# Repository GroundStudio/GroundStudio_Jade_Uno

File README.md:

GroundStudio Jade Uno
====================================

Get it from [ardushop.ro](https://ardushop.ro/ro/home/1728-placa-de-dezvoltare-jade-uno.html)

Explore all the GroundStudio products at [GroundStudio.ro](https://groundstudio.ro/)

Description
-------------------
ATMEGA328P based development board, 32kBytes of In-System Self-Programmable Flash program memory,  1kBytes EEPROM, 2kBytes Internal SRAM, 6 PWM Channels, 20 Digital Pins including 4 channel 10 bit ADC Pins and HT42B534-2 for USB comunication.

Contents
-------------------

* [/Documentation](https://github.com/GroundStudio/GroundStudio_Jade_Uno/tree/main/Documentation) -- Pinout.
* [/Hardware](https://github.com/GroundStudio/GroundStudio_Jade_Uno/tree/main/Hardware) -- Schematics, layout.

Versions
-------------------
*(Not all tags shown)*

* [REV0.2]

License
-------------------

This is released under the [Attribution-ShareAlike 4.0 International (CC BY-SA 4.0)](https://creativecommons.org/licenses/by-sa/4.0/) license. 

Please consider contributing back to help the open-source hardware community continue to thrive and grow!

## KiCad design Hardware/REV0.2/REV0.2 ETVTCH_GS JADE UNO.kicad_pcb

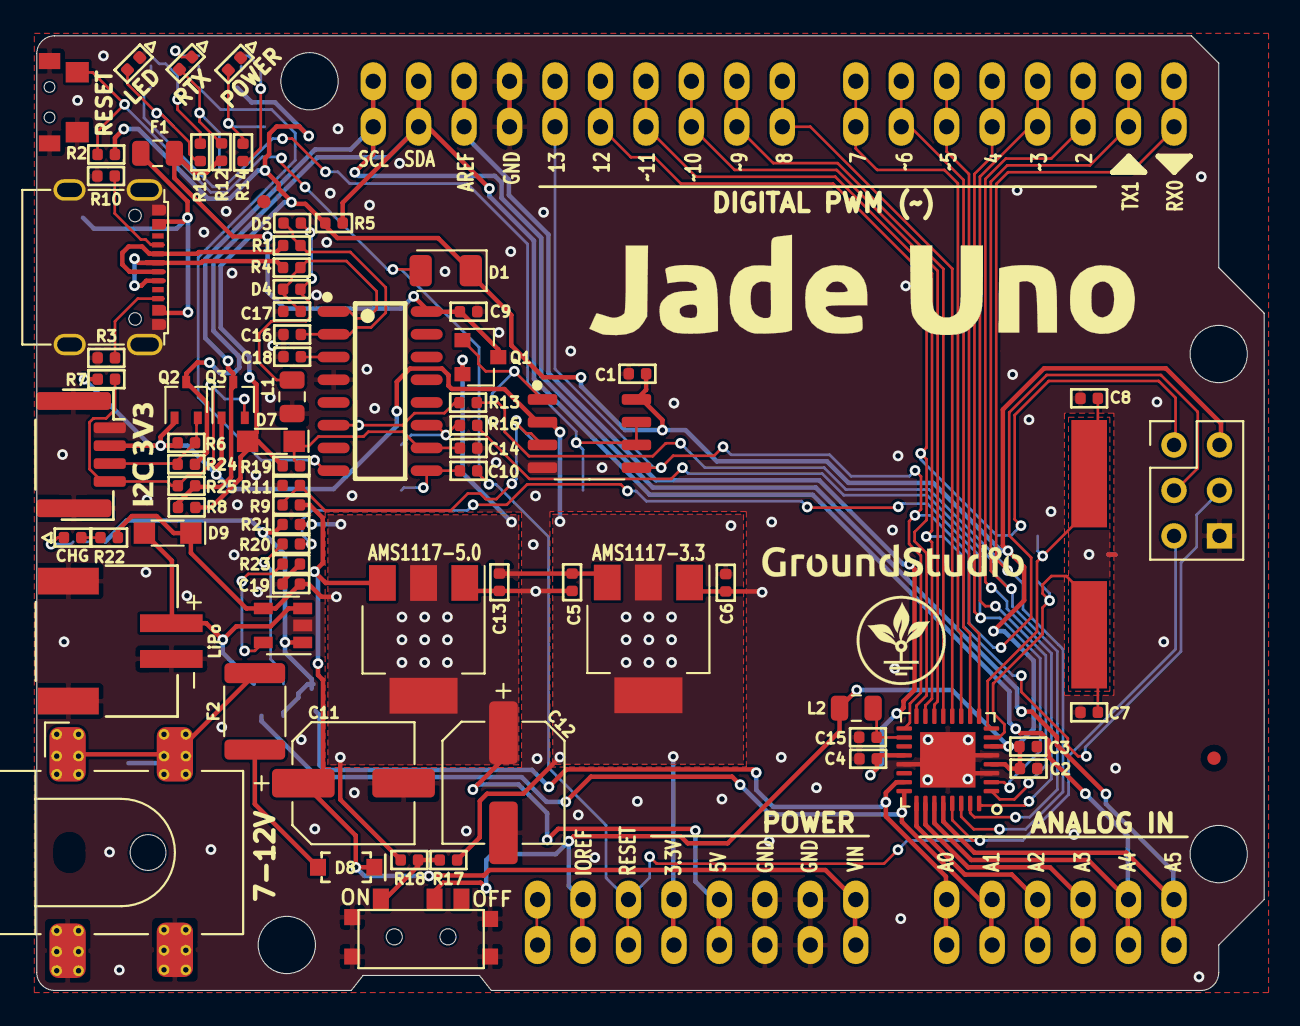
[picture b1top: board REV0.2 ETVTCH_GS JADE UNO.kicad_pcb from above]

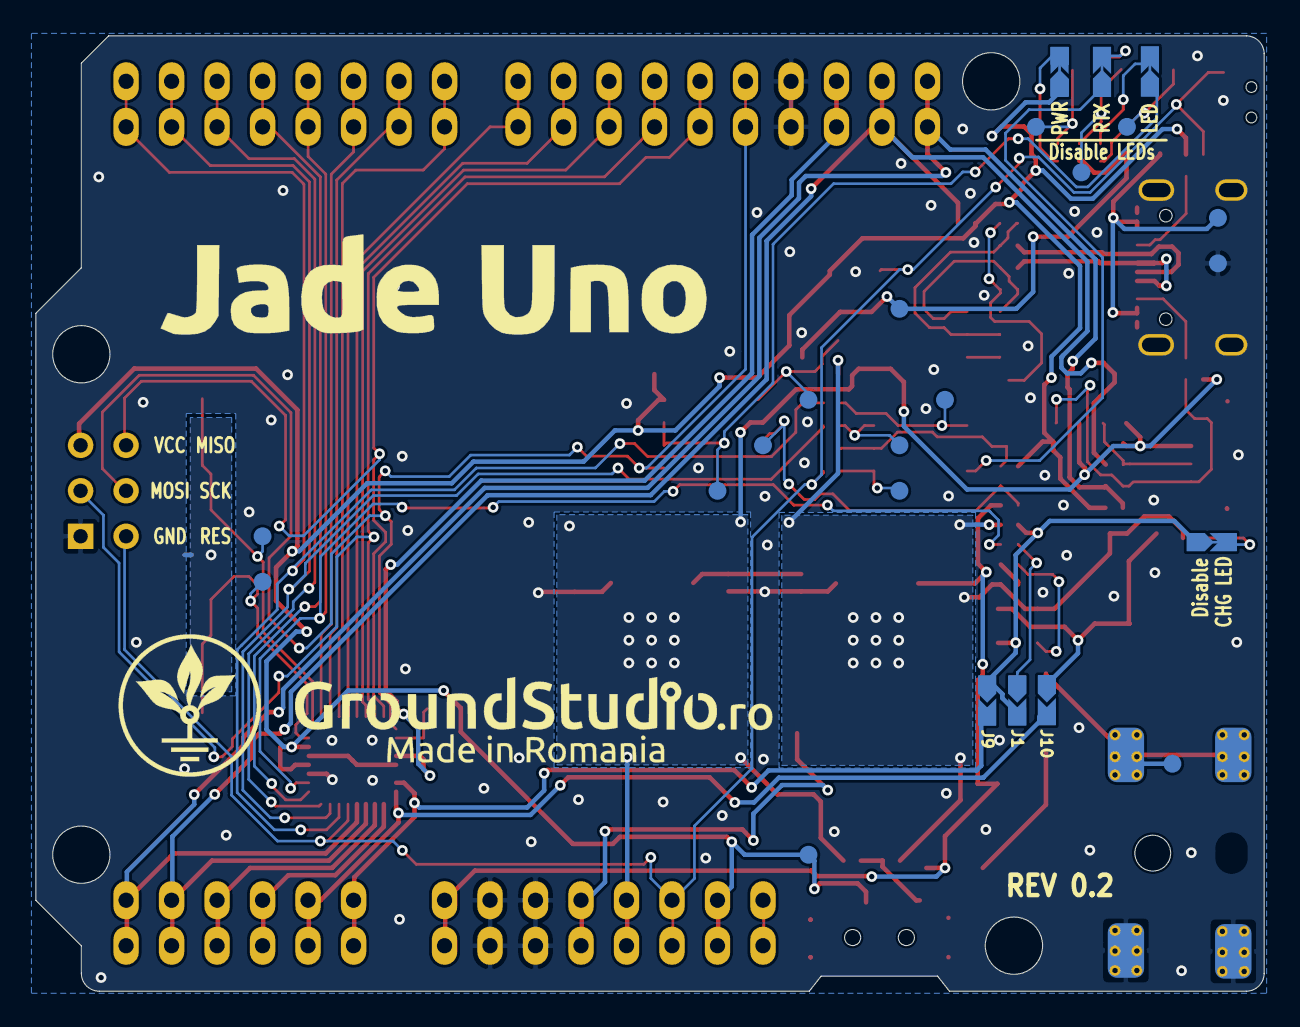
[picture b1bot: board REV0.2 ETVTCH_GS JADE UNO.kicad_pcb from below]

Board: 2 copper layers, 68.6 x 53.3 mm, 108 parts (11 on the bottom side), 66 nets.

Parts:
C1, C2, C3, C4, C9, C10, C13, C14, C15: C_0402_100nF_16V; C_0402
C5, C6: C_0402_10uF_10V; C_0402
C7, C8: C_0402_22pF_50V; C_0402
C11, C12: CP_Elec_6.3x5.4_47uF_25V; CP_Elec_6.3x5.4
C16, C17: C_0402_47pF_50V; C_0402
C18, C19: C_0402_1uF_10V; C_0402
D1: D_1206_CD1206-S01575; D_1206
D2, D6, D10: LED_0402_GREEN; LED_0402
D3: LED_0402_RED; LED_0402
D4, D5: R_0402_PS0402V014AT; R_0402
D7, D9: SOD-323 SD103AWS; SOD-323
D8: SOD-123 1N4007W; SOD-123
F1: Fuse_0805_MF-PSMF050X-2; R_0805
F2: Fuse_1812_MF-MSMF050-2; Fuse_1812
FID1, FID2: Fiducial; Fiducial_0.75mm_Mask1.5mm
IC1: SOP-16_150MIL HT42B534-2; SOP-16_150MIL
IC2: SOT23-5 BRCL4054CME; SOT-23-5
J1: CONNECT & SET D4 HIGH TO READ CHRG LVL ON A0; SolderJumper_NO
J2: SH_1x04_P1.0_H; SH__1x04_P1.00mm_Horizontal
J3: PinHeader_1x10_P2.54_V_F; PinHeader_1x10_P2.54mm_Vertical_Female
J4, J5: PinHeader_1x8_P2.54_V_F; PinHeader_1x08_P2.54mm_Vertical_Female
J6: PinHeader_1x6_P2.54_V_F; PinHeader_1x06_P2.54mm_Vertical_Female
J7: PinHeader_2x03_P2.54_V_M; PinHeader_2x03_P2.54mm_Vertical_Male
J8: DC-005-5.5-Barr_Jck_SMD; DC-005-5.5-2.0MM-SMD
J9: CONNECT TO READ CHRG LVL ON A0; SolderJumper_NO
J10: CONNECT TO READ BATT LVL ON A1; SolderJumper_NO
J11, J12, J13, J14: SolderJumper_NC
L1: L_0805_BLM21PG221SN1D; L_0805
L2: L_0805_SCMI201209X100KT; L_0805
Q1: SOT-23 IRLML6402; SOT-23
Q2, Q3: SOT-323 2N7002PW; SOT-323_SC-70
R1, R4: R_0402_33; R_0402
R2, R9, R11: R_0402_10k; R_0402
R3, R10: R_0402_5.1k; R_0402
R5, R6, R7, R8: R_0402_2.2k; R_0402
R12, R14, R15, R22: R_0402_20k; R_0402
R13, R16: R_0402_1k; R_0402
R17, R19, R24, R25: DNP; R_0402
R18: R_0402_0; R_0402
R20, R23: R_0402_2k; R_0402
R21: R_0402_820k; R_0402
SW1: K3-1296S-E2
SW2: TS24CA
TP1: TP_VBUS; TestPoint
TP2: TP_USBVCC; TestPoint
TP3: TP_LCMD; TestPoint
TP4: TP_USH; TestPoint
TP5: TP_GATE; TestPoint
TP6: TP_CMP; TestPoint
TP7: TP_TX; TestPoint
TP8: TP_LL; TestPoint
TP9: TP_RX; TestPoint
TP10: TP_ONL; TestPoint
TP11: DNP; PinHeader_1x10_P2.54mm_Vertical_Female
TP12, TP14: DNP; PinHeader_1x08_P2.54mm_Vertical_Female
TP13: TP_RXL; TestPoint
TP15: DNP; PinHeader_1x06_P2.54mm_Vertical_Female
TP16: TP_XT1; TestPoint
TP17: TP_VCC; TestPoint
TP18: TP_XT2; TestPoint
TP19: TP_DTR; TestPoint
TP23: TP_PWRIN; TestPoint
U1: SOP-8_3.9x4.9_P1.27 LM358; SOP-8_3.9x4.9mm_P1.27mm
U2: SOT-223 AMS1117-3.3; SOT-223
U3: ATmega328P-MU; QFN-32-1EP_5x5mm_P0.5mm_EP3.1x3.1mm
U5: SOT-223 AMS1117-5.0; SOT-223
USB1: USB_C 918-418K2023S40001; USB_C_C167321
X1: PH__1x02_P2.0_H; PH__1x02_P2.00mm_Horizontal
Y1: HC49-SMD 5M0-1600A2020; Crystal_HC49-SMD

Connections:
+3V3: C6.1, J2.2, J5.4, Q2.1, Q3.1, R6.1, R7.1, R17.2, TP14.4, U1.2, U2.2, U2.4
+5V: C5.1, C12.1, C13.1, C19.1, D9.1, IC2.4, J5.5, Q1.2, R18.1, R21.1, R22.2, TP14.5, U2.3, U5.2, U5.4
+BAT: D9.2, IC2.3, J10.1, X1.2
A0: J6.1, J9.2, TP15.1, U3.23
A1: J6.2, J10.2, TP15.2, U3.24
A2: J6.3, TP15.3, U3.25
A3: J6.4, TP15.4, U3.26
A4_SDA: J3.9, J6.5, Q2.3, R5.1, R24.2, TP11.9, TP15.5, U3.27
A5_SCL: J3.10, J6.6, Q3.3, R8.1, R25.2, TP11.10, TP15.6, U3.28
AREF: C4.1, J3.8, TP11.8, U3.20
CHRG: IC2.1, J1.2, J9.1, J11.1, R21.2
D2: J4.3, TP12.3, U3.32
D3: J4.4, TP12.4, U3.1
D4: J4.5, R20.1, TP12.5, U3.2
D5: J4.6, TP12.6, U3.9
D6: J4.7, TP12.7, U3.10
D7: J4.8, TP12.8, U3.11
D8: J3.1, TP11.1, U3.12
D9: J3.2, TP11.2, U3.13
D10_SS: J3.3, TP11.3, U3.14
D11_MOSI: J3.4, J7.4, TP11.4, U3.15
D12_MISO: J3.5, J7.1, TP11.5, U3.16
D13_SCK: J3.6, J7.3, TP11.6, U1.5, U3.17
D+: R4.1, USB1.A6, USB1.B6
D-: R1.1, USB1.A7, USB1.B7
GND: C1.2, C2.2, C3.2, C4.2, C5.2, C6.2, C7.1, C8.1, C9.2, C11.2, C12.2, C13.2, C14.2, C15.2, C16.1, C17.1, C18.2, C19.2, D2.1, D3.1, IC1.4, IC2.2, J2.0, J2.1, J3.7, J5.6, J5.7, J7.6, J8.3, J8.4, L1.2, R3.1, R10.2, R11.1, R23.1, SW1.4, SW2.1, SW2.2, SW2.3, TP4.~, TP11.7, TP14.6, TP14.7, U1.4, U2.1, U3.3, U3.5, U3.21, U3.33, U5.1, USB1.0, USB1.A1, USB1.A12, USB1.B1, USB1.B12, X1.0, X1.1
IC1_RX: IC1.11, R16.2, TP9.~
IC1_TX: IC1.6, R13.2, TP7.~
IOREF: C1.1, C2.1, C3.1, D1.1, D7.2, J5.2, J7.2, J13.1, L2.1, R2.2, R5.2, R8.2, R19.1, SW1.2, TP14.2, TP17.~, U1.8, U3.4, U3.6
L_CMD: J14.1, TP3.~, U1.6, U1.7
NC: J5.1, TP14.1
unnamed: C10.1, IC1.9, TP19.~
unnamed: C14.1, D7.1, IC1.10, R19.2
unnamed: C15.1, L2.2, U3.18
unnamed: C18.1, IC1.3
unnamed: D2.2, R15.2, TP8.~
unnamed: D3.2, R14.2, TP10.~
unnamed: D4.1, D5.2, L1.1
unnamed: D6.1, J12.2
unnamed: D6.2, R12.1, TP13.~
unnamed: D8.2, F2.1
unnamed: D10.1, J11.2
unnamed: D10.2, R22.1
unnamed: F2.2, J8.5, TP23.~
unnamed: IC1.8, J12.1
unnamed: IC2.5, R23.2
unnamed: J1.1, R20.2
unnamed: J2.3, Q2.2, R6.2, R24.1
unnamed: J2.4, Q3.2, R7.2, R25.1
unnamed: J13.2, R14.1
unnamed: J14.2, R15.1
unnamed: Q1.1, TP5.~, U1.1
unnamed: R3.2, USB1.B5
unnamed: R10.1, USB1.A5
unnamed: R9.1, R11.2, TP6.~, U1.3
unnamed: R17.1, R18.2, SW1.3
RES: C10.2, D1.2, J5.3, J7.5, R2.1, SW2.4, TP14.3, U3.29
RX0: J4.1, R13.1, TP12.1, U3.30
TX1: J4.2, R16.1, TP12.2, U3.31
UD+: C17.2, D4.2, IC1.1, R4.2
UD-: C16.2, D5.1, IC1.2, R1.2
USB_VCC: C9.1, F1.1, IC1.16, Q1.3, R12.2, TP2.~
VBUS: F1.2, TP1.~, USB1.A4, USB1.A9, USB1.B4, USB1.B9
VIN: C11.1, D8.1, J5.8, R9.2, TP14.8, U5.3
XTAL1: C7.2, TP16.~, U3.7, Y1.1
XTAL2: C8.2, TP18.~, U3.8, Y1.2

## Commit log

2022-08-09 - initial commit
2022-08-26 - added schematic pdf file
2022-08-26 - added "Kicad6" to revision folder name
2023-03-08 - fixed the wrong size values. - added I2C 3V3 connector in description. - changed number of digital pins to 16 in description. - highlighted A4 & A5 pins to not be used.
2023-03-15 Update README.md
    - removed references to "library"
2023-10-26 - added .step 3D file of the board
